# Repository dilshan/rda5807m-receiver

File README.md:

# FM stereo radio receiver with RDS

This tuner circuit is a quick prototype which I build to test the *RDA5807M* FM radio tuner IC. *RDA5807M* is a single-chip tuner IC with RDS and MPX decoder, and it equipped with I2C interface for control. 

This receiver builds around Atmel's *ATmega16A* 8-bit MCU. The output stage of this design consists of *AN7147N*, 2×5.3W audio power amplifier. 

Based on the specifications of the switching-regulator and power amplifier, this circuit can drive between 9V to 20V DC input. The most recommended working voltage for this receiver is 12V.

As mentioned above this design is a quick prototype to test the features of *RDA5807M* tuner. Most of the parameters of this tuner are hardcoded in the firmware and not exposed in UI. 

-------------------------------------------------------------------------------------------------------------------------

The firmware source codes of this project are released under the terms of the [MIT license](https://github.com/dilshan/rda5807m-receiver/blob/master/LICENSE). All the design files and schematics are released under the terms of the [Creative Commons - Attribution 4.0 International license](https://creativecommons.org/licenses/by/4.0/).

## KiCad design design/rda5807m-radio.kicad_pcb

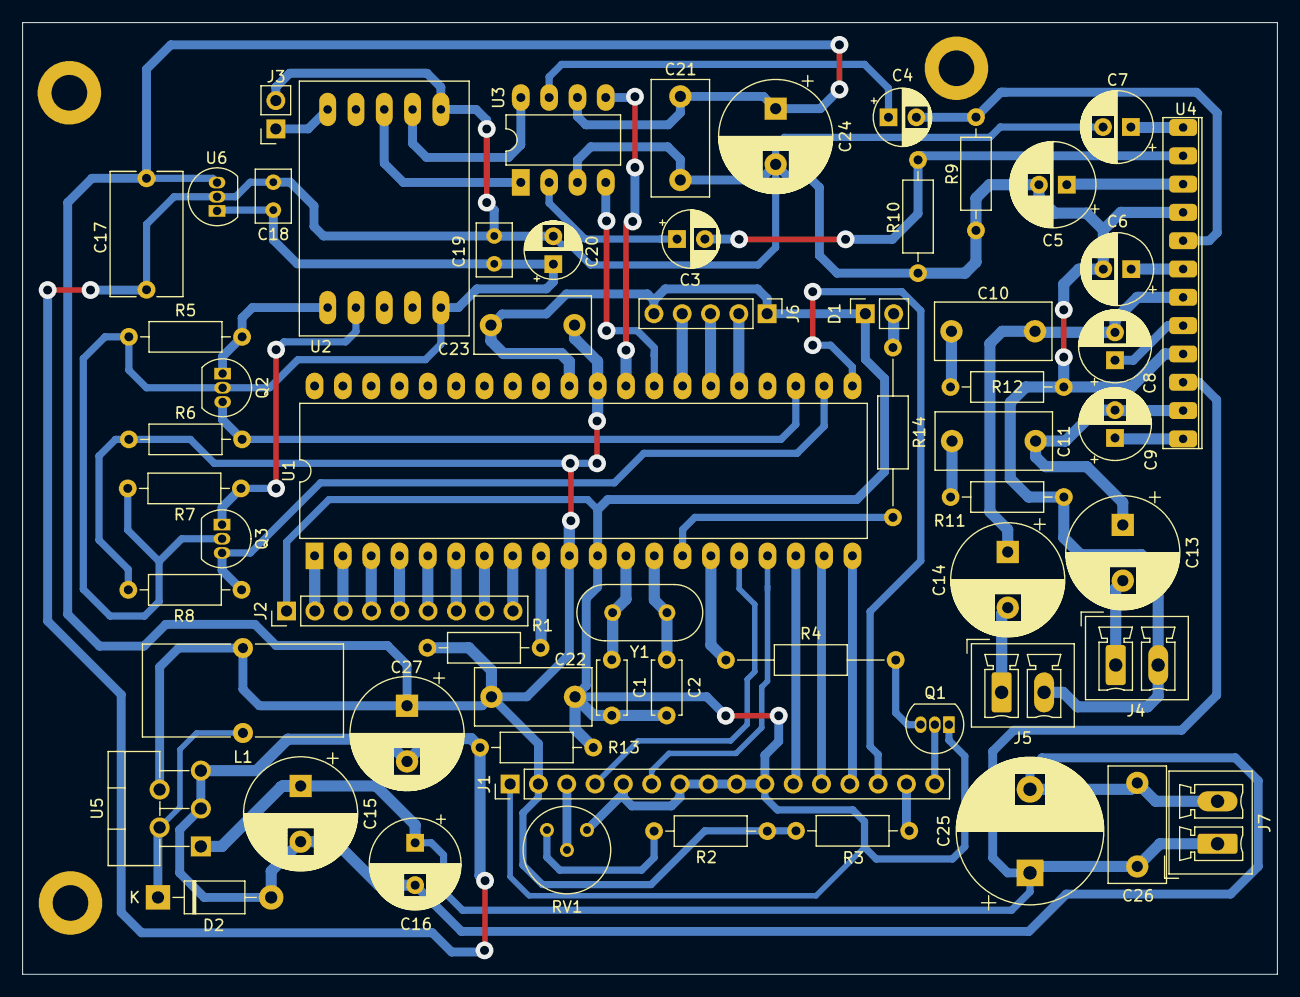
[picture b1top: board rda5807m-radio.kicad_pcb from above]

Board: 2 copper layers, 112.6 x 85.4 mm, 64 parts (0 on the bottom side), 58 nets.

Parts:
 : MountingHole_3.2mm_M3_ISO7380_Pad
 #2,  #3: MountingHole_3.2mm_M3_ISO7380_Pad
C1, C2: 12pF; C_Disc_D4.7mm_W2.5mm_P5.00mm
C3, C4, C20: 10MFD; CP_Radial_D5.0mm_P2.50mm
C5: 100MFD; CP_Radial_D7.5mm_P2.50mm
C6, C7: 33MFD; CP_Radial_D6.3mm_P2.50mm
C8, C9: 47MFD; CP_Radial_D6.3mm_P2.50mm
C10, C11, C21, C22, C23, C26: 0.1MFD; C_Rect_L10.3mm_W5.0mm_P7.50mm_MKS4
C13, C14, C15: 470MFD; CP_Radial_D10.0mm_P5.00mm
C16: 220MFD; CP_Radial_D8.0mm_P3.80mm
C17: 0.22MFD; C_Rect_L11.0mm_W6.3mm_P10.00mm_MKT
C18, C19: 0.1MFD; C_Rect_L4.6mm_W3.0mm_P2.50mm_MKS02_FKP02
C24, C27: 1000MFD; CP_Radial_D10.0mm_P5.00mm
C25: 2200MFD; CP_Radial_D13.0mm_P7.50mm
D1: LED; PinSocket_1x02_P2.54mm_Vertical
D2: 1N5819; D_DO-41_SOD81_P10.16mm_Horizontal
J1: LCD; PinHeader_1x16_P2.54mm_Vertical
J2: BTN-IN; PinHeader_1x09_P2.54mm_Vertical
J3: ANT; PinSocket_1x02_P2.54mm_Vertical
J4: SPK-L; PhoenixContact_MCV_1,5_2-G-3.81_1x02_P3.81mm_Vertical
J5: SPK-R; PhoenixContact_MCV_1,5_2-G-3.81_1x02_P3.81mm_Vertical
J6: ROT-ENC; PinHeader_1x05_P2.54mm_Vertical
J7: DC-IN; PhoenixContact_MCV_1,5_2-G-3.81_1x02_P3.81mm_Vertical
L1: 33uH; L_Toroid_Vertical_L17.8mm_W8.1mm_P7.62mm_Bourns_5700
Q1: 2SC945; TO-92_Inline
Q2, Q3: STK7000; TO-92_Inline
R1: 22K; R_Axial_DIN0207_L6.3mm_D2.5mm_P10.16mm_Horizontal
R2: 1K; R_Axial_DIN0207_L6.3mm_D2.5mm_P10.16mm_Horizontal
R3: 680R; R_Axial_DIN0207_L6.3mm_D2.5mm_P10.16mm_Horizontal
R4: 22K; R_Axial_DIN0207_L6.3mm_D2.5mm_P15.24mm_Horizontal
R5, R6, R7, R8: 10K; R_Axial_DIN0207_L6.3mm_D2.5mm_P10.16mm_Horizontal
R9, R10: 47K; R_Axial_DIN0207_L6.3mm_D2.5mm_P10.16mm_Horizontal
R11, R12: 1R; R_Axial_DIN0207_L6.3mm_D2.5mm_P10.16mm_Horizontal
R13: 0R; R_Axial_DIN0207_L6.3mm_D2.5mm_P10.16mm_Horizontal
R14: 560R; R_Axial_DIN0207_L6.3mm_D2.5mm_P15.24mm_Horizontal
RV1: 10K; Potentiometer_Bourns_3339H_Vertical
U1: ATmega16A; DIP-40_W15.24mm_LongPads
U2: RDA5807M; RDA5807M-MODULE
U3: M62429; DIP-8_W7.62mm_LongPads
U4: AN7147; SIP-12-2P
U5: LM2596T-5; TO-220-5_P3.4x3.7mm_StaggerOdd_Lead3.8mm_Vertical
U6: L78L33; TO-92_Inline
Y1: 4.00MHz; Crystal_HC49-U_Vertical

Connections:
+3V3: C18.1, C19.1, C20.1, Q2.2, Q3.2, R5.1, R7.1, U2.5, U6.1
+5V: C17.1, C21.1, C22.1, C23.1, C24.1, C27.1, J1.2, L1.2, R1.1, R2.2, R3.1, R6.1, R8.1, U1.10, U1.30, U3.6, U5.4, U6.3
AF-OUT-L: C13.2, J4.1
AF-OUT-R: C14.2, J5.1
ANT: J3.1, U2.10
GND: C5.2, C6.2, C7.2, C15.2, C16.2, C17.2, C18.2, C19.2, C20.2, C21.2, C24.2, C25.2, C26.2, C27.2, D2.2, J3.2, J4.2, J5.2, J7.2, R9.2, R10.2, R11.1, R12.2, R13.2, U2.6, U3.3, U4.4, U4.9, U5.3, U5.5, U6.2
GNDD: C1.2, C2.2, C22.2, C23.2, D1.1, J1.1, J1.5, J1.7, J1.8, J1.9, J1.10, J2.1, J6.1, J6.5, Q1.1, R13.1, RV1.3, U1.11, U1.31
LCD-BK: R4.1, U1.15
LCD-DATA4: J1.11, U1.18
LCD-DATA5: J1.12, U1.19
LCD-DATA6: J1.13, U1.20
LCD-DATA7: J1.14, U1.21
LCD-EN: J1.6, U1.17
LCD-RS: J1.4, U1.16
MEM-CH1: J2.4, U1.3
MEM-CH2: J2.5, U1.4
MEM-CH3: J2.6, U1.5
MEM-CH4: J2.7, U1.6
MEM-CH5: J2.8, U1.7
MEM-CH6: J2.9, U1.8
unnamed: C1.1, U1.12, Y1.2
unnamed: C2.1, U1.13, Y1.1
unnamed: C3.1, U3.2
unnamed: C4.1, U3.7
unnamed: C5.1, U4.3
unnamed: C6.1, U4.6
unnamed: C7.1, U4.1
unnamed: C8.1, U4.8
unnamed: C9.1, U4.12
unnamed: C8.2, C10.1, C14.1, U4.7
unnamed: C10.2, R12.1
unnamed: C11.1, R11.2
unnamed: C9.2, C11.2, C13.1, U4.11
unnamed: D1.2, R14.1
unnamed: D2.1, L1.1, U5.2
unnamed: J1.3, RV1.2
unnamed: J1.15, R3.2
unnamed: J1.16, Q1.2
unnamed: Q1.3, R4.2
unnamed: R1.2, U1.9
unnamed: R2.1, RV1.1
OUT-L-FM: U2.8, U3.1
OUT-R-FM: U2.7, U3.8
ROTARY-BTN: J6.2, U1.25
ROTARY-SW-A: J6.3, U1.26
ROTARY-SW-B: J6.4, U1.27
SCL: Q3.3, R8.2, U1.22
SCL-FM: Q3.1, R7.2, U2.2
SDA: Q2.3, R6.2, U1.23
SDA-FM: Q2.1, R5.2, U2.1
STEREO-IND: R14.2, U1.14
TUNE-DOWN: J2.3, U1.2
TUNE-UP: J2.2, U1.1
VCC: C15.1, C16.1, C25.1, C26.1, J7.1, U4.10, U5.1
VOL-CLK: U1.29, U3.5
VOL-DATA: U1.28, U3.4
VOL-L: C3.2, R10.1, U4.2
VOL-R: C4.2, R9.1, U4.5

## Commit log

2019-09-12 Initial version of design files and firmware source files.
2019-09-12 Format readme file.
2019-09-12 Fix issues in license statement.
2019-09-12 Refactor code in main modules.
2019-09-12 Add image resources related to the project.
2019-09-12 Link prototype image with readme file.
2021-05-05 add sym-lib-table
